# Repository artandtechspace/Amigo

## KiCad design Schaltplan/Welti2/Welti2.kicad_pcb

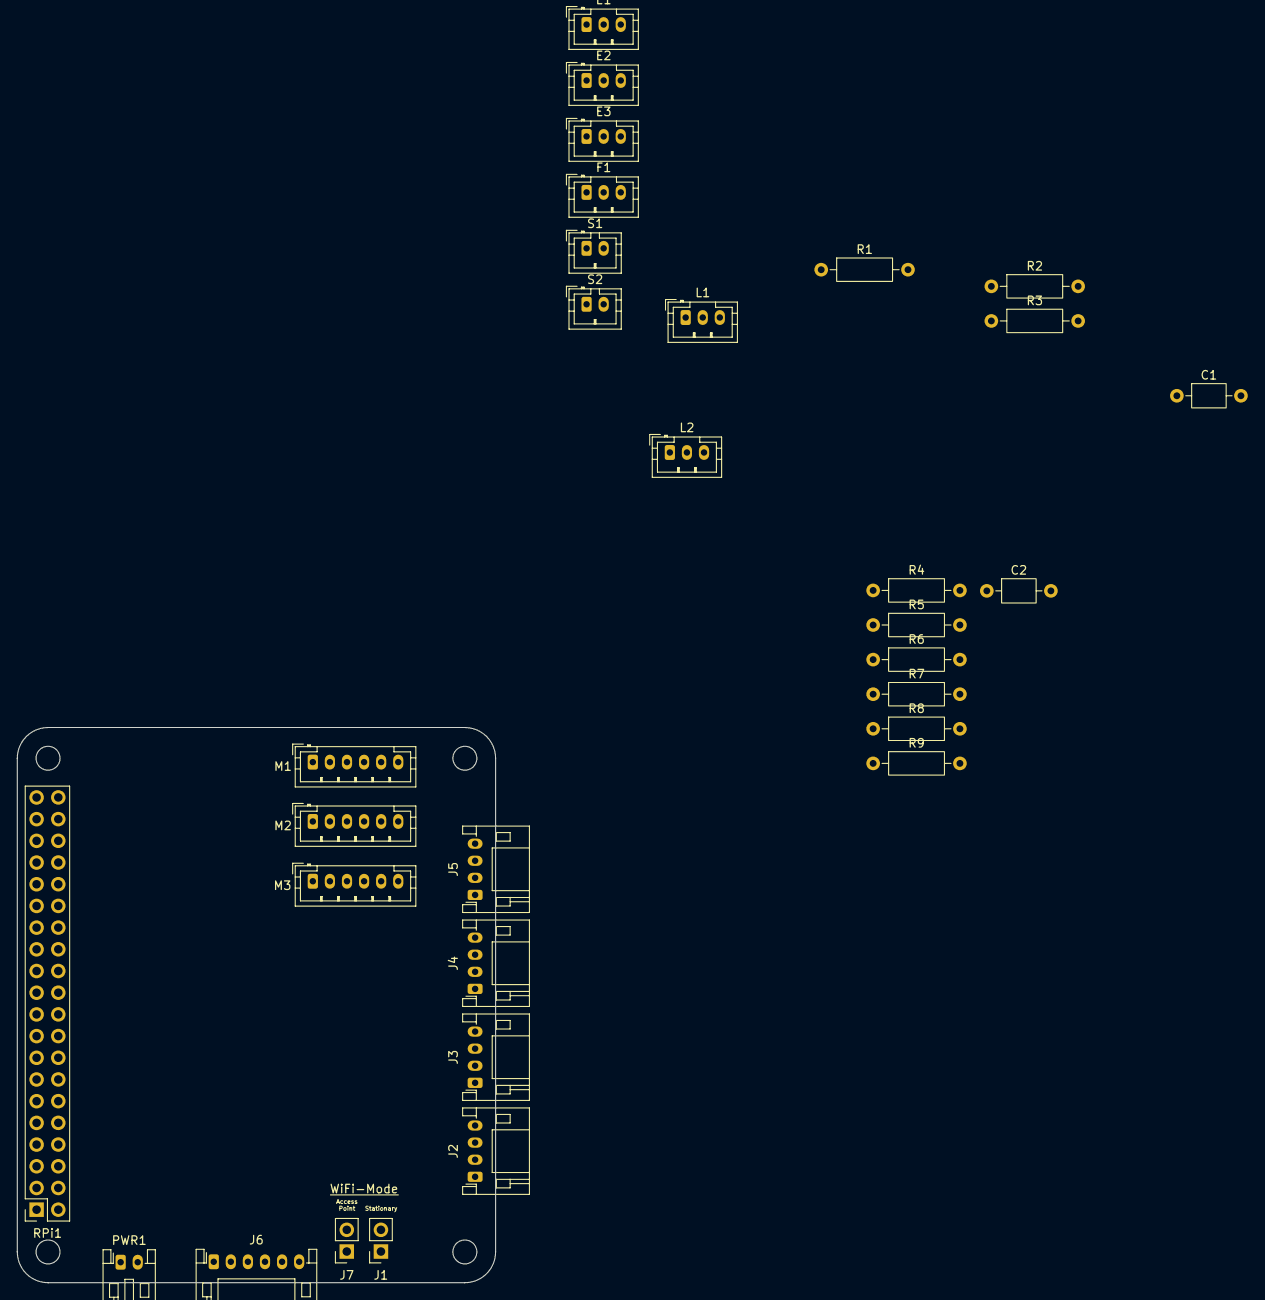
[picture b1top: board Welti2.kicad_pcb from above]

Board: 2 copper layers, 56.0 x 65.0 mm, 31 parts (0 on the bottom side), 22 nets, no tracks yet.

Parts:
C1, C2: C; C_Axial_L3.8mm_D2.6mm_P7.50mm_Horizontal
E1: Limit Switches Motor 1; JST_PH_B3B-PH-K_1x03_P2.00mm_Vertical
E2: Limit Switches Motor 2; JST_PH_B3B-PH-K_1x03_P2.00mm_Vertical
E3: Limit Switches Motor 3; JST_PH_B3B-PH-K_1x03_P2.00mm_Vertical
F1: Fog-Device; JST_PH_B3B-PH-K_1x03_P2.00mm_Vertical
J1: Dummy; PinSocket_1x02_P2.54mm_Vertical
J2: PWM-Feedback-1; JST_PH_S4B-PH-K_1x04_P2.00mm_Horizontal
J3: PWM-Feedback-2; JST_PH_S4B-PH-K_1x04_P2.00mm_Horizontal
J4: PWM-Feedback-3; JST_PH_S4B-PH-K_1x04_P2.00mm_Horizontal
J5: PWM-Feedback-4; JST_PH_S4B-PH-K_1x04_P2.00mm_Horizontal
J6: PWM-Module; JST_PH_S6B-PH-K_1x06_P2.00mm_Horizontal
J7: Boot-Wifi-Config-Pin; PinSocket_1x02_P2.54mm_Vertical
L1: WS2812B Ring; JST_PH_B3B-PH-K_1x03_P2.00mm_Vertical
L2: WS2812B Stripe; JST_PH_B3B-PH-K_1x03_P2.00mm_Vertical
M1: Motor 1; JST_PH_B6B-PH-K_1x06_P2.00mm_Vertical
M2: Motor 2; JST_PH_B6B-PH-K_1x06_P2.00mm_Vertical
M3: Motor 3; JST_PH_B6B-PH-K_1x06_P2.00mm_Vertical
PWR1: Power-Supply; JST_PH_S2B-PH-K_1x02_P2.00mm_Horizontal
R1, R2, R3, R4, R5, R6, R7, R8, R9: 10k; R_Axial_DIN0207_L6.3mm_D2.5mm_P10.16mm_Horizontal
RPi1: Raspberry Pi; PinSocket_2x20_P2.54mm_Vertical_RpiPins
S1: Pre-Switch; JST_PH_B2B-PH-K_1x02_P2.00mm_Vertical
S2: Main-Switch; JST_PH_B2B-PH-K_1x02_P2.00mm_Vertical

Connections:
/BTN_LIMIT_M1_END: E1.2, R9.2, RPi1.19
/BTN_LIMIT_M1_START: E1.3, R8.1, RPi1.21
/BTN_LIMIT_M2_END: E2.2, R7.2, RPi1.32
/BTN_LIMIT_M2_START: E2.3, R6.1, RPi1.22
/BTN_LIMIT_M3_END: E3.2, R5.2, RPi1.18
/BTN_LIMIT_M3_START: E3.3, R4.1, RPi1.16
/FOG_DEVICE: F1.3, RPi1.15
/I2C_SCL: J6.4, RPi1.5
/I2C_SDA: J6.3, RPi1.3
/LED_RING: L1.3, RPi1.11
/LED_STRIPE: L2.3, RPi1.13
/MAIN_SWITCH: C2.1, R1.1, RPi1.33, S2.2
/PRE_SWITCH: C1.1, R2.1, RPi1.31, S1.2
/PWM_MOTOR_1_LEFT: J2.1, M1.2
/PWM_MOTOR_1_RIGHT: J2.2, M1.1
/PWM_MOTOR_2_LEFT: J2.3, M2.2
/PWM_MOTOR_2_RIGHT: J2.4, M2.1
/PWM_MOTOR_3_LEFT: J3.1, M3.2
/PWM_MOTOR_3_RIGHT: J3.2, M3.1
/WIFI_CONFIG_SWITCH: J7.2, R3.1, RPi1.29
GND: C1.2, C2.2, E1.1, E2.1, E3.1, F1.2, J6.6, J7.1, L1.2, L2.2, M1.6, M2.6, M3.6, PWR1.2, RPi1.6, S1.1, S2.1
VCC: F1.1, J6.2, L1.1, L2.1, M1.3, M1.4, M1.5, M2.3, M2.4, M2.5, M3.3, M3.4, M3.5, PWR1.1, R1.2, R2.2, R3.2, R4.2, R5.1, R6.2, R7.1, R8.2, R9.1, RPi1.2

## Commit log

2025-08-07 Added Motor
2025-08-07 Added limit switch
2025-08-07 Name switch
2025-08-07 Create PGM-37DC12_77.stl
    Add Motor with Gear
2025-08-07 - Motor LP ausgetauscht! - & noch irgendwas!!!!! is halt so! bla! LG carl <- is müde!
2025-08-08 Added modified approximated version of the termal printer
2025-08-09 sämtliches
    ja halt das wasda steht
2025-08-12 Added more sketches, added constructions, split stl's and freecad files
2025-08-12 Added Powersupply
2025-08-15 Added PCB, added further parts and added parts into combined freecad project
